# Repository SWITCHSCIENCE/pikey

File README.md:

# Pikey

This is 30 keys Keyboard and enclosure with integrated stand for Raspberry Pi 2,3,3+ and 3.5 inch display.

* PCB
	* Gerber data
	* KiCad project
	* Schematic
	* Artwork
	* BOM
* Firmware
	* QMK Keyboard source file
* Document
	* Not yet.
* 3D model
	* STL file
	* [Tinkercad](https://www.tinkercad.com/things/kkT37oe7HXW)

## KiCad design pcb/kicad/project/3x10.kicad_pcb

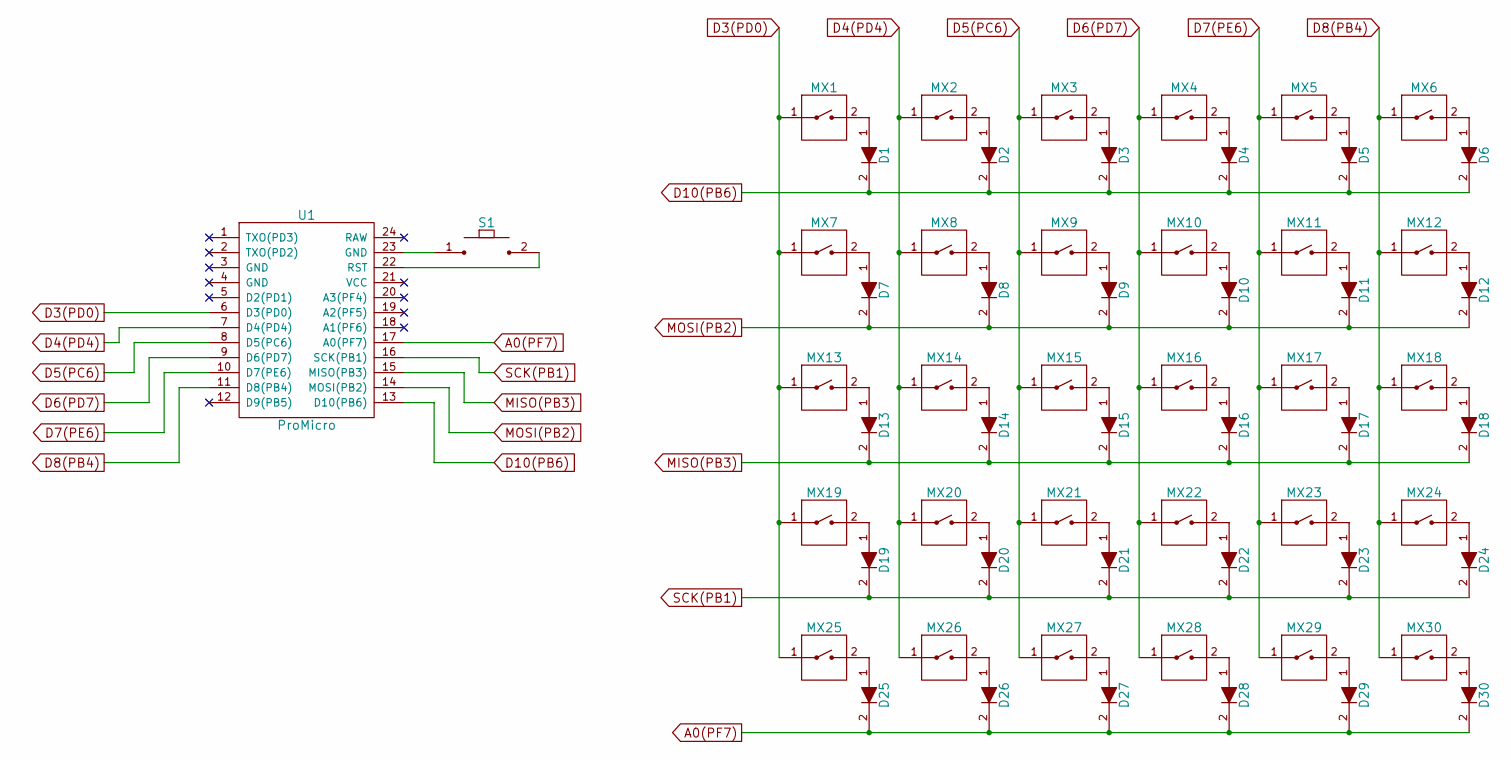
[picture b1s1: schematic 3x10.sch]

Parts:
D1, D2, D3, D4, D5, D6, D7, D8, D9, D10, D11, D12, D13, D14, D15, D16, D17, D18, D19, D20, D21, D22, D23, D24, D25, D26, D27, D28, D29, D30: diode
MX1, MX2, MX3, MX4, MX5, MX6, MX7, MX8, MX9, MX10, MX11, MX12, MX13, MX14, MX15, MX16, MX17, MX18, MX19, MX20, MX21, MX22, MX23, MX24, MX25, MX26, MX27, MX28, MX29, MX30: keyswitch
S1: tactswitch
U1: ProMicro; promicro

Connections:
A0(PF7): D25.2, D26.2, D27.2, D28.2, D29.2, D30.2, U1.17 (A0(PF7))
D3(PD0): MX1.1, MX7.1, MX13.1, MX19.1, MX25.1, U1.6 (D3(PD0))
D4(PD4): MX2.1, MX8.1, MX14.1, MX20.1, MX26.1, U1.7 (D4(PD4))
D5(PC6): MX3.1, MX9.1, MX15.1, MX21.1, MX27.1, U1.8 (D5(PC6))
D6(PD7): MX4.1, MX10.1, MX16.1, MX22.1, MX28.1, U1.9 (D6(PD7))
D7(PE6): MX5.1, MX11.1, MX17.1, MX23.1, MX29.1, U1.10 (D7(PE6))
D8(PB4): MX6.1, MX12.1, MX18.1, MX24.1, MX30.1, U1.11 (D8(PB4))
D10(PB6): D1.2, D2.2, D3.2, D4.2, D5.2, D6.2, U1.13 (D10(PB6))
MISO(PB3): D13.2, D14.2, D15.2, D16.2, D17.2, D18.2, U1.15 (MISO(PB3))
MOSI(PB2): D7.2, D8.2, D9.2, D10.2, D11.2, D12.2, U1.14 (MOSI(PB2))
unnamed: D1.1, MX1.2
unnamed: D2.1, MX2.2
unnamed: D3.1, MX3.2
unnamed: D4.1, MX4.2
unnamed: D5.1, MX5.2
unnamed: D6.1, MX6.2
unnamed: D7.1, MX7.2
unnamed: D8.1, MX8.2
unnamed: D9.1, MX9.2
unnamed: D10.1, MX10.2
unnamed: D11.1, MX11.2
unnamed: D12.1, MX12.2
unnamed: D13.1, MX13.2
unnamed: D14.1, MX14.2
unnamed: D15.1, MX15.2
unnamed: D16.1, MX16.2
unnamed: D17.1, MX17.2
unnamed: D18.1, MX18.2
unnamed: D19.1, MX19.2
unnamed: D20.1, MX20.2
unnamed: D21.1, MX21.2
unnamed: D22.1, MX22.2
unnamed: D23.1, MX23.2
unnamed: D24.1, MX24.2
unnamed: D25.1, MX25.2
unnamed: D26.1, MX26.2
unnamed: D27.1, MX27.2
unnamed: D28.1, MX28.2
unnamed: D29.1, MX29.2
unnamed: D30.1, MX30.2
unnamed: S1.1, U1.23 (GND)
unnamed: S1.2, U1.22 (RST)
SCK(PB1): D19.2, D20.2, D21.2, D22.2, D23.2, D24.2, U1.16 (SCK(PB1))

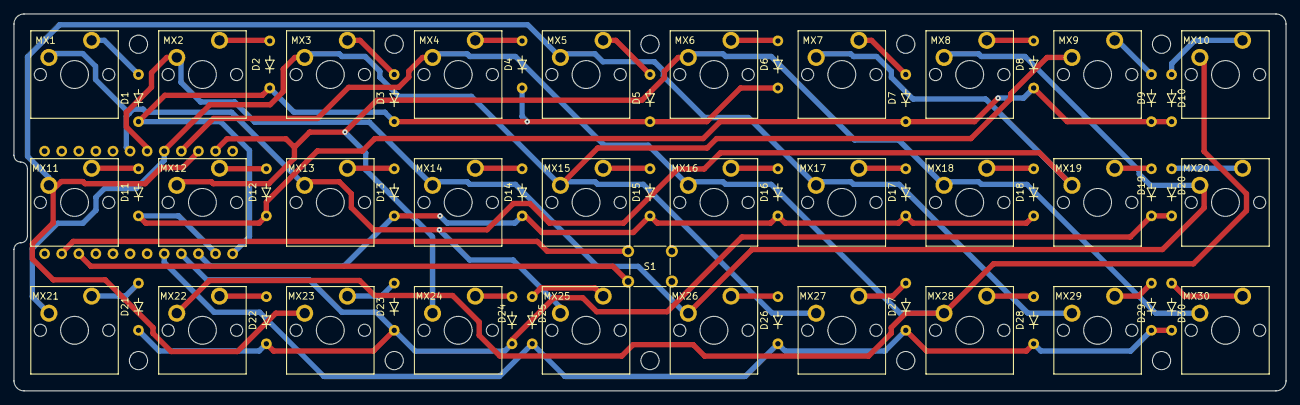
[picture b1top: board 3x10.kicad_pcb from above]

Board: 2 copper layers, 189.0 x 56.0 mm, 72 parts (1 on the bottom side), 43 nets.

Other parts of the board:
h1, h2, h3, h4, h5, h6, h7, h8, h9, h10: MountingHole_2.7mm_M2.5

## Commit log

2018-07-13 first
2018-07-13 add BOM
2018-07-14 0.8mmのトレースに変更、不要なKiCadファイルの削除、ガーバー再作成
2018-07-15 add 3D model
2018-07-15 Add USB hole to 3D
2018-07-15 Update Readme and add docs
2018-07-16 コンテンツ書き始めた
2018-07-17 内容追加
2018-07-19 3d update
2018-07-19 pcb update
2018-07-19 add gerber.zip
2018-07-19 update 3D model
2018-07-19 add firmware
2018-07-19 change name to pikey3x10
2018-08-03 changed Readme and BOM
2018-08-03 delete
2018-08-03 add sorry
2018-08-04 add readme for 3d
